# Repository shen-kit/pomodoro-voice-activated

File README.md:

# Schematic

## Parts List

- [capacitors](https://www.digikey.com.au/en/products/detail/nextgen-components/0402W105M6R3HI/18677006) 
	- 10nF: [0402B103K500HI](https://www.digikey.com.au/en/products/detail/nextgen-components/0402B103K500HI/22601905)
	- 0.1uF: [0402B104K250HI](https://www.digikey.com.au/en/products/detail/nextgen-components/0402B104K250HI/14670955)
	- 1uF: [0402W105M6R3HI](https://www.digikey.com.au/en/products/detail/nextgen-components/0402W105M6R3HI/18677006), 
	- 4.7uF: [0402W475M6R3HI](https://www.digikey.com.au/en/products/detail/nextgen-components/0402W475M6R3HI/18677043)
	- 10uF: [0402W106M6R3HI](https://www.digikey.com.au/en/products/detail/nextgen-components/0402W106M6R3HI/18677011)
	- footprint: 0402
	- 220uF electrolytic: [Wurth Elektronik 865080245009](https://www.digikey.com.au/en/products/detail/w%C3%BCrth-elektronik/865080245009/5728087?s=N4IgTCBcDaIBwDYCsAGOKwBZUoJwgF0BfIA)
	- footprint: 6.6 (dia) x 7.7 (height)
- LEDs: [green](https://www.digikey.com.au/en/products/detail/xinglight/XL-1608PGC-06/25673192) | [red](https://www.digikey.com.au/en/products/detail/xinglight/XL-1608VRC-06/25673309)
	- green: XL-1608PGC-06
    - red: XL-1608VRC-06
	- footprint: 0603
- [schottky diode](PMEG2015EH,115):
	- PMEG2015EH,115
- resistors (CR0603)
	- 330: [CR0603-FX-3300ELF](https://www.digikey.com.au/en/products/detail/bourns-inc/CR0603-FX-3300ELF/3783948)
	- 3.3k: [CR0603-JW-332ELF](https://www.digikey.com.au/en/products/detail/bourns-inc/CR0603-JW-332ELF/3784358)
	- 5.1k: [CR0603-FX-5101ELF](https://www.digikey.com.au/en/products/detail/bourns-inc/CR0603-FX-5101ELF/3784064)
	- 10k: [CR0603-FX-1002ELF](https://www.digikey.com.au/en/products/detail/bourns-inc/CR0603-FX-1002ELF/3593188)
	- 100k: [CR0603-FX-1003ELF](https://www.digikey.com.au/en/products/detail/bourns-inc/CR0603-FX-1003ELF/3593193)
- [push button](https://www.digikey.com.au/en/products/detail/c-k/PTS636SK25SMTR-LFS/10071735)
	- PTS636SK25SMTR LFS
- [usb receptacle](https://au.mouser.com/en/ProductDetail/Same-Sky/UJ20-C-H-G-SMT-1-P16-TR)
	- 179-UJ20CHGSMT1P16TR
- JST PH2.0 connector
- IRLML6402
- APK2112K-3.3
- MCP73831-2-OT
- ESP32-S3-WROOM-1-N16R8

## GPIO Connections

| Function   | ESP32-S3 GPIO |
| ---------- | ------------- |
| OLED_SDA   | 10            |
| OLED_SCL   | 9             |
| MIC_SCK    | 5             |
| MIC_WS     | 6             |
| MIC_SD     | 7             |
| ENCODER_A  | 14            |
| ENCODER_B  | 13            |
| ENCODER_SW | 12            |
| LED_DATA   | 16            |

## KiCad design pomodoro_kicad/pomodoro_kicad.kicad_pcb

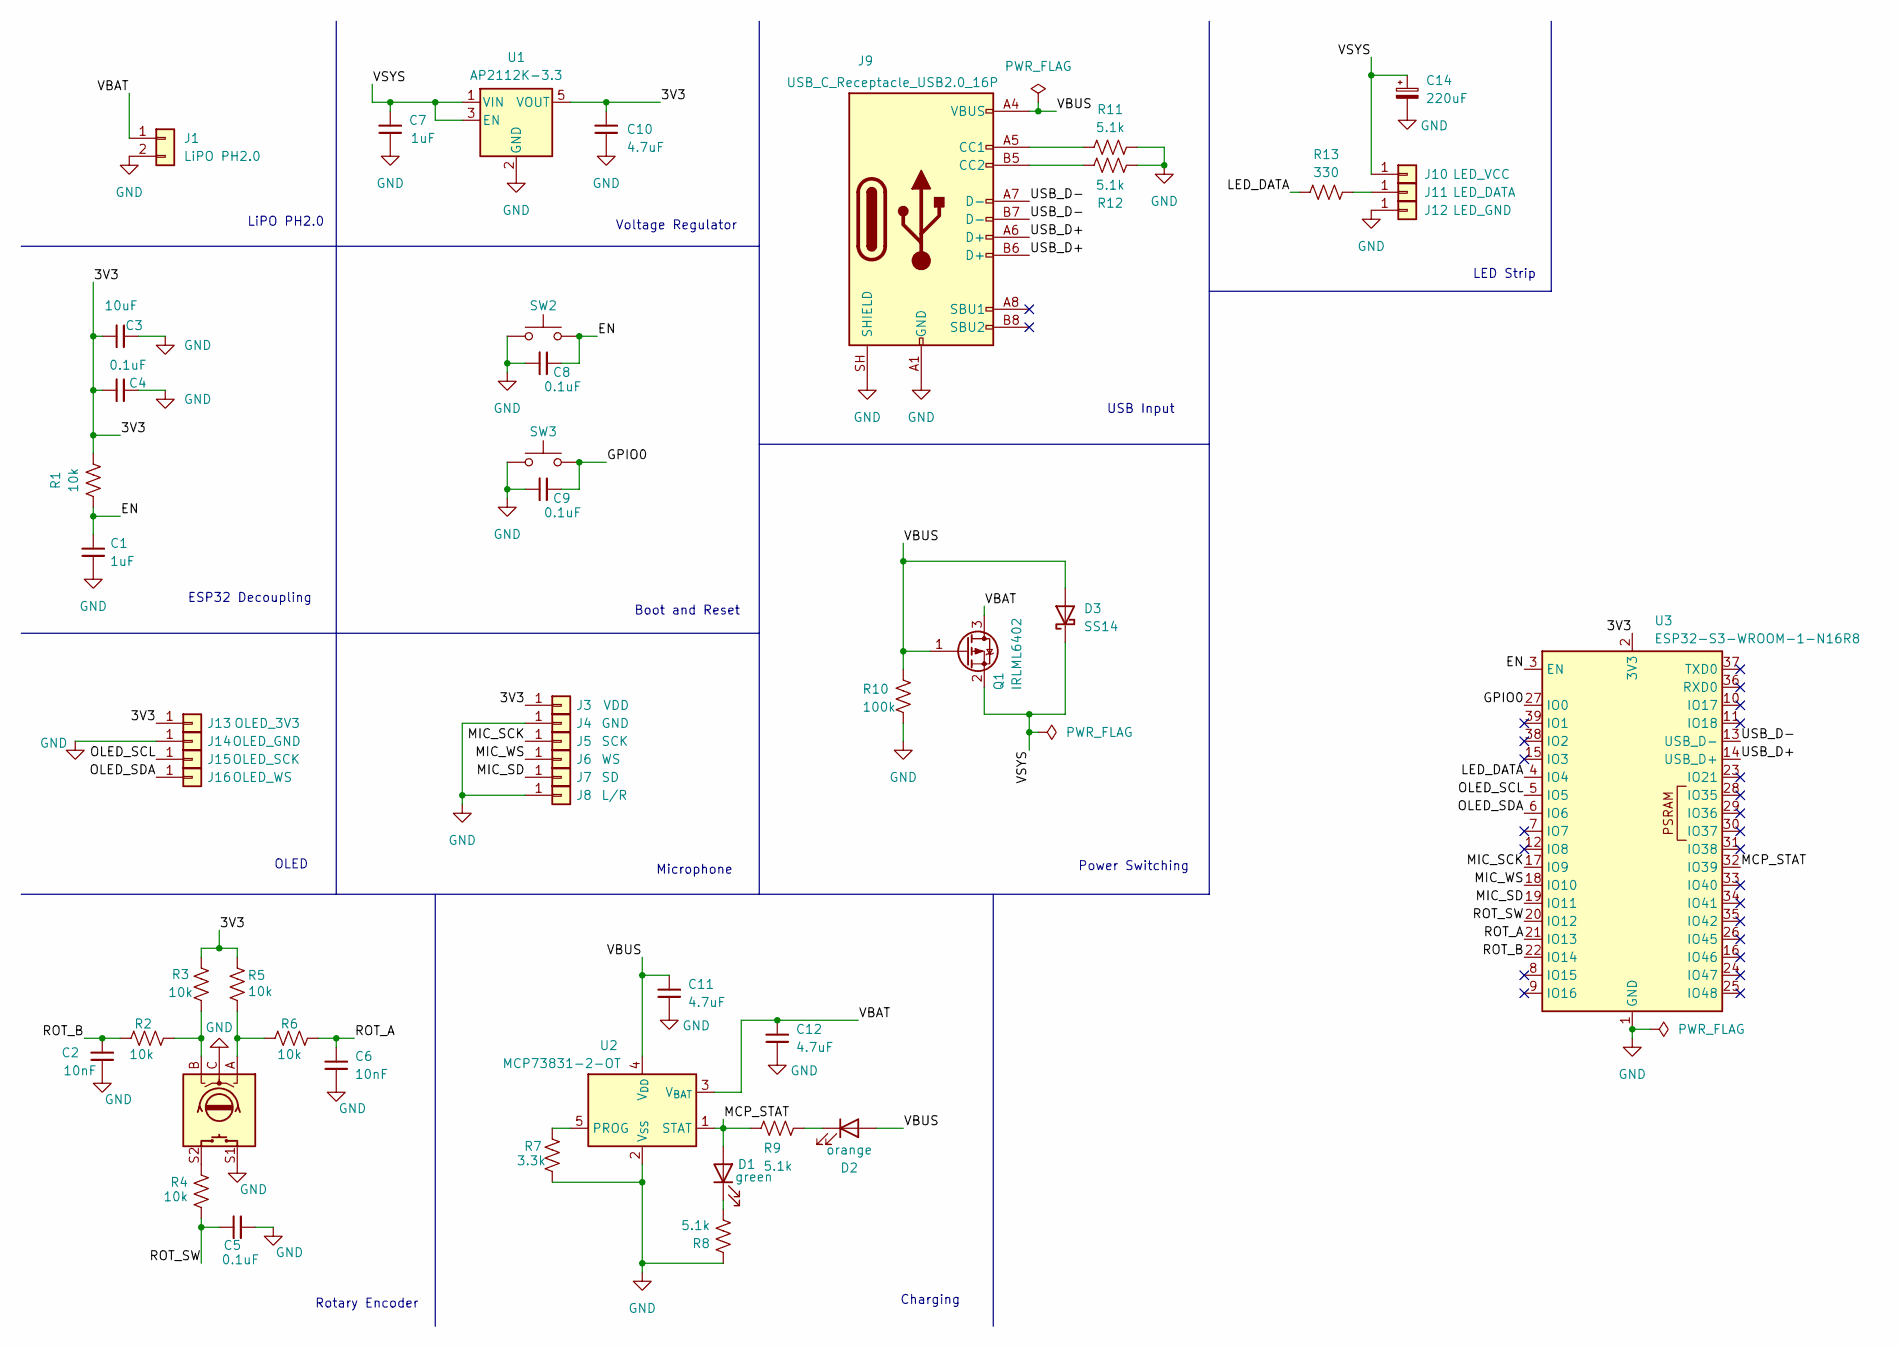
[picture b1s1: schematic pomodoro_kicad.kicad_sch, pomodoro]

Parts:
C1, C7: 1uF; C_0402_1005Metric
C2, C6: 10nF; C_0402_1005Metric
C3: 10uF; C_0402_1005Metric
C4, C5, C8, C9: 0.1uF; C_0402_1005Metric
C10, C11, C12: 4.7uF; C_0402_1005Metric
C14: 220uF; CP_Elec_6.3x7.7
D1: green; LED_0603_1608Metric
D2: orange; LED_0603_1608Metric
D3: SS14; D_SOD-123F
J1: LiPO PH2.0; JST_PH_S2B-PH-SM4-TB_1x02-1MP_P2.00mm_Horizontal
J3: VDD; TestPoint_THTPad_D2.0mm_Drill1.0mm
J4: GND; TestPoint_THTPad_D2.0mm_Drill1.0mm
J5: SCK; TestPoint_THTPad_D2.0mm_Drill1.0mm
J6: WS; TestPoint_THTPad_D2.0mm_Drill1.0mm
J7: SD; TestPoint_THTPad_D2.0mm_Drill1.0mm
J8: L/R; TestPoint_THTPad_D2.0mm_Drill1.0mm
J9: USB_C_Receptacle_USB2.0_16P; USB_C_Receptacle_HRO_TYPE-C-31-M-12
J10: LED_VCC; TestPoint_THTPad_D2.0mm_Drill1.0mm
J11: LED_DATA; TestPoint_THTPad_D2.0mm_Drill1.0mm
J12: LED_GND; TestPoint_THTPad_D2.0mm_Drill1.0mm
J13: OLED_3V3; TestPoint_THTPad_D2.0mm_Drill1.0mm
J14: OLED_GND; TestPoint_THTPad_D2.0mm_Drill1.0mm
J15: OLED_SCK; TestPoint_THTPad_D2.0mm_Drill1.0mm
J16: OLED_WS; TestPoint_THTPad_D2.0mm_Drill1.0mm
Q1: IRLML6402; SOT-23-3
R1, R2, R3, R4, R5, R6: 10k; R_0603_1608Metric
R7: 3.3k; R_0603_1608Metric
R8, R9, R11, R12: 5.1k; R_0603_1608Metric
R10: 100k; R_0603_1608Metric
R13: 330; R_0603_1608Metric
SW1: RotaryEncoder_Switch; rotaryEncoder
SW2, SW3: SW_Tactile_SPST_NO_Straight_CK_PTS636Sx25SMTRLFS
U1: AP2112K-3.3; SOT-23-5
U2: MCP73831-2-OT; SOT-23-5
U3: ESP32-S3-WROOM-1-N16R8; ESP32-S3-WROOM-1

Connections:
/3V3: C3.1, C4.1, C10.1, J3.1 (Pin_1_1), J13.1 (Pin_1_1), R1.1, R3.1, R5.1, U1.5 (VOUT), U3.2 (3V3)
/EN: C1.1, C8.1, R1.2, SW2.2, U3.3 (EN)
/GPIO0: C9.1, SW3.2, U3.27 (IO0)
/LED_DATA: R13.2, U3.4 (IO4)
/MCP_STAT: D1.2 (A), R9.1, U2.1 (STAT), U3.32 (IO39)
/MIC_SCK: J5.1 (Pin_1_1), U3.17 (IO9)
/MIC_SD: J7.1 (Pin_1_1), U3.19 (IO11)
/MIC_WS: J6.1 (Pin_1_1), U3.18 (IO10)
/OLED_SCL: J15.1 (Pin_1_1), U3.5 (IO5)
/OLED_SDA: J16.1 (Pin_1_1), U3.6 (IO6)
/ROT_A: C6.2, R6.1, U3.21 (IO13)
/ROT_B: C2.2, R2.1, U3.22 (IO14)
/ROT_SW: C5.2, R4.1, U3.20 (IO12)
/USB_D+: J9.A6 (D+), J9.B6 (D+), U3.14 (USB_D+)
/USB_D-: J9.A7 (D-), J9.B7 (D-), U3.13 (USB_D-)
/VBAT: C12.1, J1.1, Q1.3 (D), U2.3 (V_{BAT})
/VBUS: C11.1, D2.2 (A), D3.2 (A), J9.A4 (VBUS), J9.A9 (VBUS), J9.B4 (VBUS), J9.B9 (VBUS), Q1.1 (G), R10.1, U2.4 (V_{DD})
/VSYS: C7.1, C14.1, D3.1 (K), J10.1 (Pin_1_1), Q1.2 (S), U1.1 (VIN), U1.3 (EN)
GND: C1.2, C2.1, C3.2, C4.2, C5.1, C6.1, C7.2, C8.2, C9.2, C10.2, C11.2, C12.2, C14.2, J1.2, J4.1 (Pin_1_1), J8.1 (Pin_1_1), J9.A1 (GND), J9.A12 (GND), J9.B1 (GND), J9.B12 (GND), J9.SH (SHIELD), J12.1 (Pin_1_1), J14.1 (Pin_1_1), R7.1, R8.2, R10.2, R11.1, R12.2, SW1.C, SW1.S1, SW2.1, SW3.1, U1.2 (GND), U2.2 (V_{SS}), U3.1 (GND), U3.40 (GND), U3.41 (GND)
unnamed: D1.1 (K), R8.1
unnamed: D2.1 (K), R9.2
unnamed: J9.A5 (CC1), R11.2
unnamed: J9.B5 (CC2), R12.1
unnamed: J11.1 (Pin_1_1), R13.1
unnamed: R2.2, R3.2, SW1.B
unnamed: R4.2, SW1.S2
unnamed: R5.2, R6.2, SW1.A
unnamed: R7.2, U2.5 (PROG)

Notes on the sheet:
Power Switching
LED Strip
OLED
Voltage Regulator
Charging
Microphone
LiPO PH2.0
ESP32 Decoupling
USB Input
Rotary Encoder
Boot and Reset

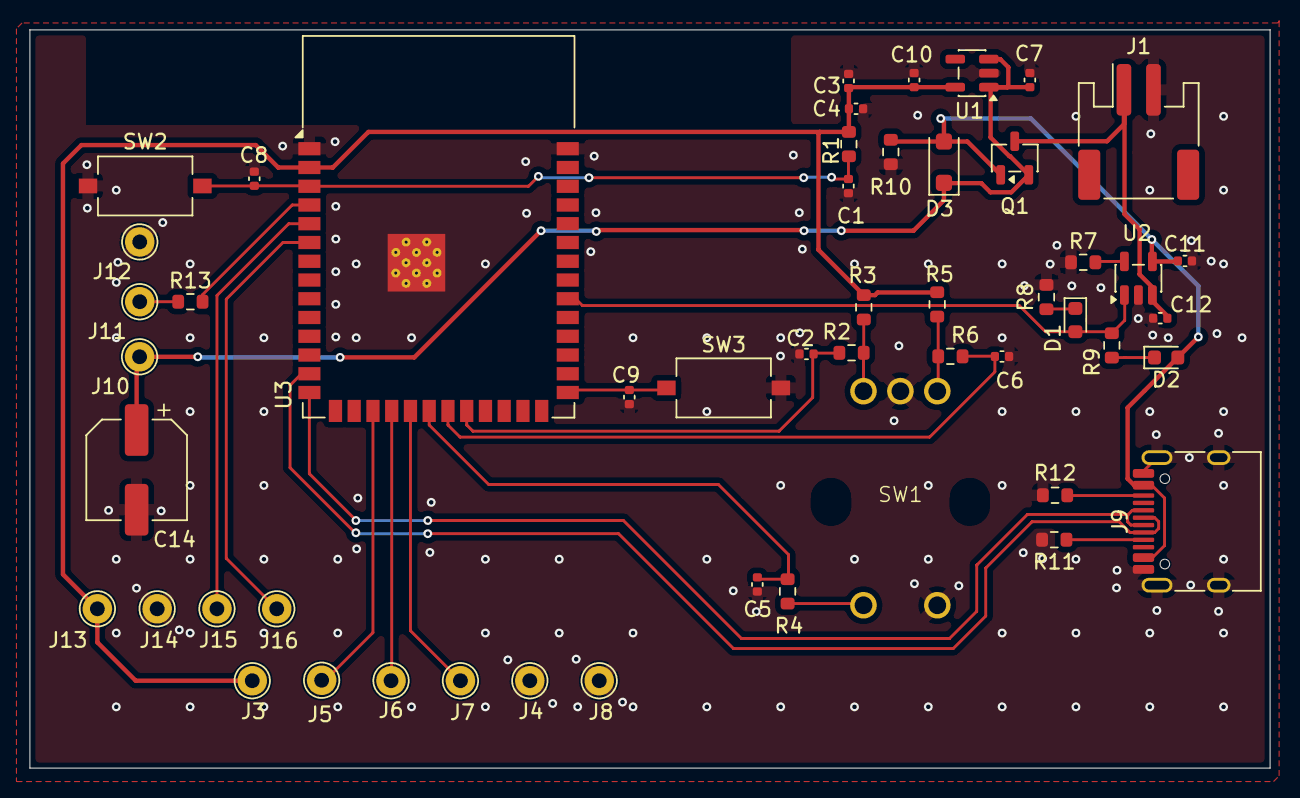
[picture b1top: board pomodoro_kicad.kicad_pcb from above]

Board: 2 copper layers, 84.0 x 50.0 mm, 51 parts (0 on the bottom side), 28 nets.
